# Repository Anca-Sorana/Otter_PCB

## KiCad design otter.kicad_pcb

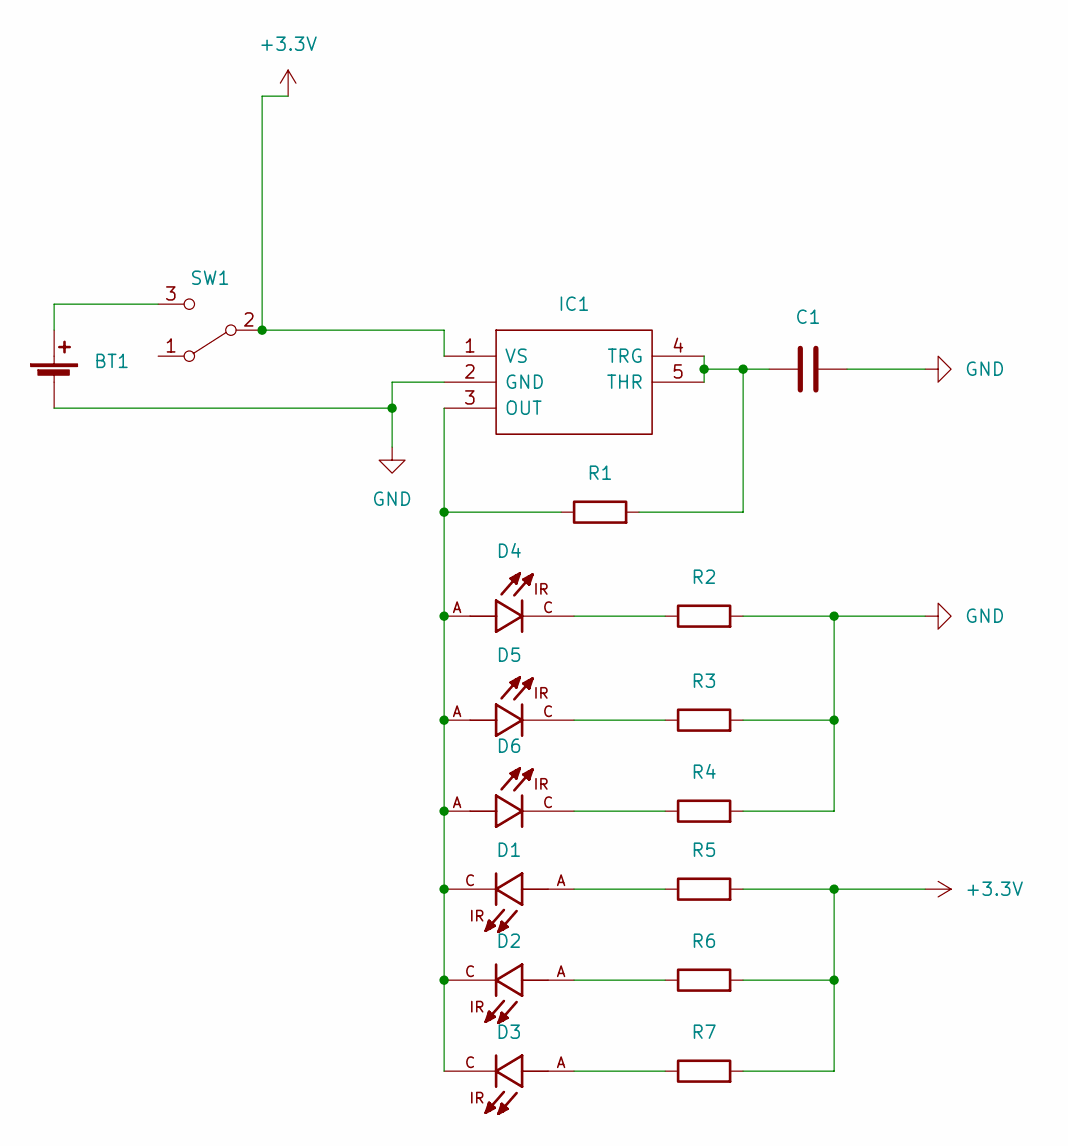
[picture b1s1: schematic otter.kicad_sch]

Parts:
BT1: Battery_Cell; BatteryHolder_Keystone_3034_1x20mm
C1: C; C_0201_0603Metric
D1, D2, D3, D4, D5, D6: VSMB294008RG; DIO_VSMB294008RG; PARTREV 1.1
IC1: MIC1555YM5-TR; SOT95P280X145-5N; Mouser Part Number 998-MIC1555YM5TR
R1, R2, R3, R4, R5, R6, R7: R; R_0603_1608Metric
SW1: SW_SPDT; SW_SPDT_PCM12

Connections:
+3.3V: IC1.1 (VS), R5.2, R6.2, R7.2, SW1.2 (B)
GND: BT1.2 (-), C1.2, IC1.2 (GND), R2.2, R3.2, R4.2
unnamed: BT1.1 (+), SW1.3 (C)
unnamed: C1.1, IC1.4 (TRG), IC1.5 (THR), R1.2
unnamed: D1.A, R5.1
unnamed: D1.C, D2.C, D3.C, D4.A, D5.A, D6.A, IC1.3 (OUT), R1.1
unnamed: D2.A, R6.1
unnamed: D3.A, R7.1
unnamed: D4.C, R2.1
unnamed: D5.C, R3.1
unnamed: D6.C, R4.1

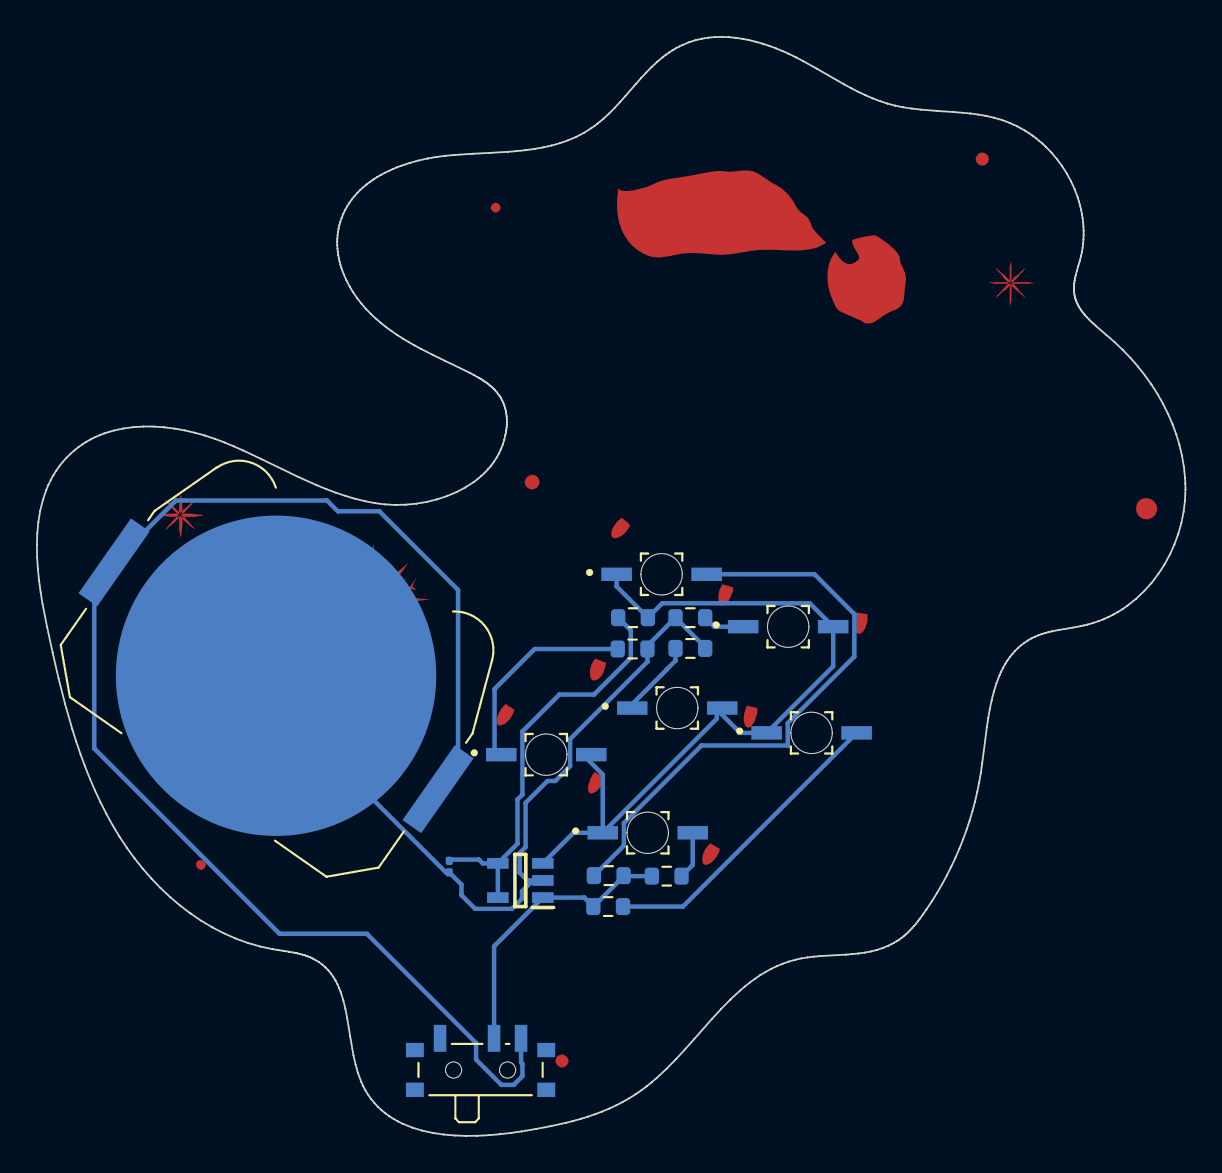
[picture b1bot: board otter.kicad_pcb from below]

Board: 2 copper layers, 63.8 x 61.1 mm, 17 parts (17 on the bottom side), 11 nets.
